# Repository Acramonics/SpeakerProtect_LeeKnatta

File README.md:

Speaker protect circuit from Lee Knatta
https://www.diyaudio.com/community/threads/improved-speaker-protection-circuit.302384/page-6

### PSU:

The power supply is just a full bridge rectifier with storage capacitor. The capacitor C81 should be large and able to withstand the voltage.
The AC loss detection uses half bridge rectifier D81 and D82 to make Q80 conduct and prevent C82 from charging up.
Once the AC fails, C82 charges through R83 and Q81 starts conducting. The "shutdown" is triggered by pulling low.

Assembly notes:
R82 is somewhat superfluous and could be left away with R81 = 100k instead. There are many such useless resistors in the design.
R84 aims to limit discharge current of C82 and may not be really necessary given that Q80 collector current is limited by the large value of R81.
R80 and C80 are optional and just a snubber for taming resonance of the transformer with the rectifier bridge. For now, I didn't install those components.

Debug:
Apply AC to the circuit and measure the supply voltage. Should be 1.4*Vac minus 1V4.
Also install (pull-up) resistor R1 (different schematic page) and measure the voltage at the "shutdown" terminal = supply voltage.
After removal of the AC, the voltage at the at the shutdown terminal should fall to 0V quickly while the supply voltage declines slowly.

### Startup Delay

Resistor R1 charges capacitor C1 until the voltage is high enough for the Schmid trigger Q1 / Q2 to change state.
R2 is just for limiting discharge current in case the "shutdown" terminal is used by external switches / relays to avoid contact damage.
I revised the resistor values around the Schmid trigger to improve low voltage operation.

Notes:
Q4 and Q5 were added to enable DC detection only after the start-up so that DC events during start-up don't trigger the circuitry. This seemed a good idea with the "latch" mode operation enabled, but is a brain fart because once a DC event occurs, the DC detection circuitry is being disabled and may not be able to discharge C1 enough. Furthermore, if the DC error persists (blown output stage) the circuitry enters a hiccup mode, which is highly undesirable. Short Q4 and Q5 as illustrated.
I came to the conclusion that the "latch" mode is not such a great idea for typical applications. More on this on another page.

Debug:
The start-up delay is roughly 12 seconds with the component values shown.
After the delay, the voltage at the collector of Q2 goes high, enabling attached circuitry (if any).
On AC loss, the voltage should go low quickly.

### Status indication and latch

You may recognize that there are two current sources that can be switched on by pulling R23 / R26 low, thus enabling the reference voltage generation of the CCS.
The DC detection connects to the left through R20 and R21.
In case of a DC event, Q20 + Q21 output a few mA into the red LED that indicates that there is a DC error at the moment.
At the same time, Q22 and Q23 output a few mA into the yellow LED and if the components around Q24 are installed, the Q22 / Q23 CCS is kept on after C20 has charged up. The circuitry around Q24 is for the latch operation and keeps the Q22 / Q23 CCS on until switch S1 resets the latch.
The whole LED indicator and latch circuitry has been helpful in the past to debug the operation, but it is kind of impractical to manually reset the circuit in case a DC event has happened. On the other hand side, such events should be very rare. Without the latch enabled, the module re-connects the loudspeaker 12 seconds after the DC error has cleared. No issues with hiccup here. LED indicators are nice, but require a lot of components.

This time, I neither wanted any LED indicators, nor latch operation and just installed R20 + R21 and wired the cathode of D20 to the collector of Q25, bypassing all the circuitry on this page.

There are two options of LED indicators (if desired):
The traffic light thee color LED that makes most sense with the latch mode and a plain red / green LED.
For the R / G LED, the red one takes the place of the yellow one, thus the Q20 / Q21 circuitry should be left away.

3 LED colors:
Green = Loudspeaker connected, everything okay
Red = Acute DC error, loudspeaker disconnected
Yellow = Acute DC error and once red is off: DC error history, loudspeaker disconnected

2 LED colors:
Green = Loudspeaker connected, everything okay
Red = Either acute DC error or DC error history, loudspeaker disconnected

### DC Detection

Here is the DC detection of the left channel. The right channel is identical.

I reverted some connections back to the initial scheme, got rid of some useless components and optimized some component values.
Note that all crossed out components are superfluous and not installed.
I believe I explained the circuit earlier, but here we go again:

Q42 / Q44 and Q43 / Q45 are just current sources, which are switched on by Q40 / Q41 if the amplifier output (left side of the schematic) is DC long enough to charge C40 through R40.
C40 should be >33uF and <56uF. I installed 56uF.
I haven't completed AC tests, thus C41 / C42 are not optimized. A few nF / tens of nF may help to avoid false triggering on high frequency signals. If optimized, this bug may be a feature for oscillation detection maybe. Simulation shows that the detection is less sensitive to high frequencies with updated component values, thus maybe it even works well without C41 / C42.
The two CCS drive current through U40 and U41, which then activate the circuitry on the previous schematic page by pulling low the "DC_FAULT" node.

Galvanic isolation of U40 / U41 is great, but has a price (commercially). There is no need for low on resistance of the opto-couplers, which allows to pick cheaper ones.

DC detection threshold is roughly 3V3. This is good because it avoids false triggering on asymmetric signals (some music may be asymmetric) and this is bad because in case the amplifier has huge DC offset, the drivers may be damaged even at low voltage. There are more sensitive DC detection circuits in case this is a concern.

### Solid state relays

Now both photovoltaic drivers are controlled by the same current source Q60 / Q61.
The current source is switched on by the Schmid trigger.
Having the drivers in series also increases the minimum supply voltage required: The module works with >6VDC.
The output voltage of the photovoltaic drivers should be 13-14V roughly.

Power MOSFETs need to be chosen according to amplifier supply voltage / power and market situation.
Vds needs to be higher than the rail to rail power supply voltage. Lowest on resistance is desirable for lowest distortion.

The 18V Zeners protect the gates and the MOVs should be rated lower than the Vds of the MOSFET.

If the module is powered with >50V roughly, Q61 should have a small radiator.

Note the symbol for U60 / U61 is weird because I designed SMD / THT combo footprint and this is why there are 16 terminals.

# OK light

This would be the optional green LED indicating that everything is okay:

Q70 switches on the CCS Q71 / Q72, which dumps a few mA through the green LED.
Nothing special.

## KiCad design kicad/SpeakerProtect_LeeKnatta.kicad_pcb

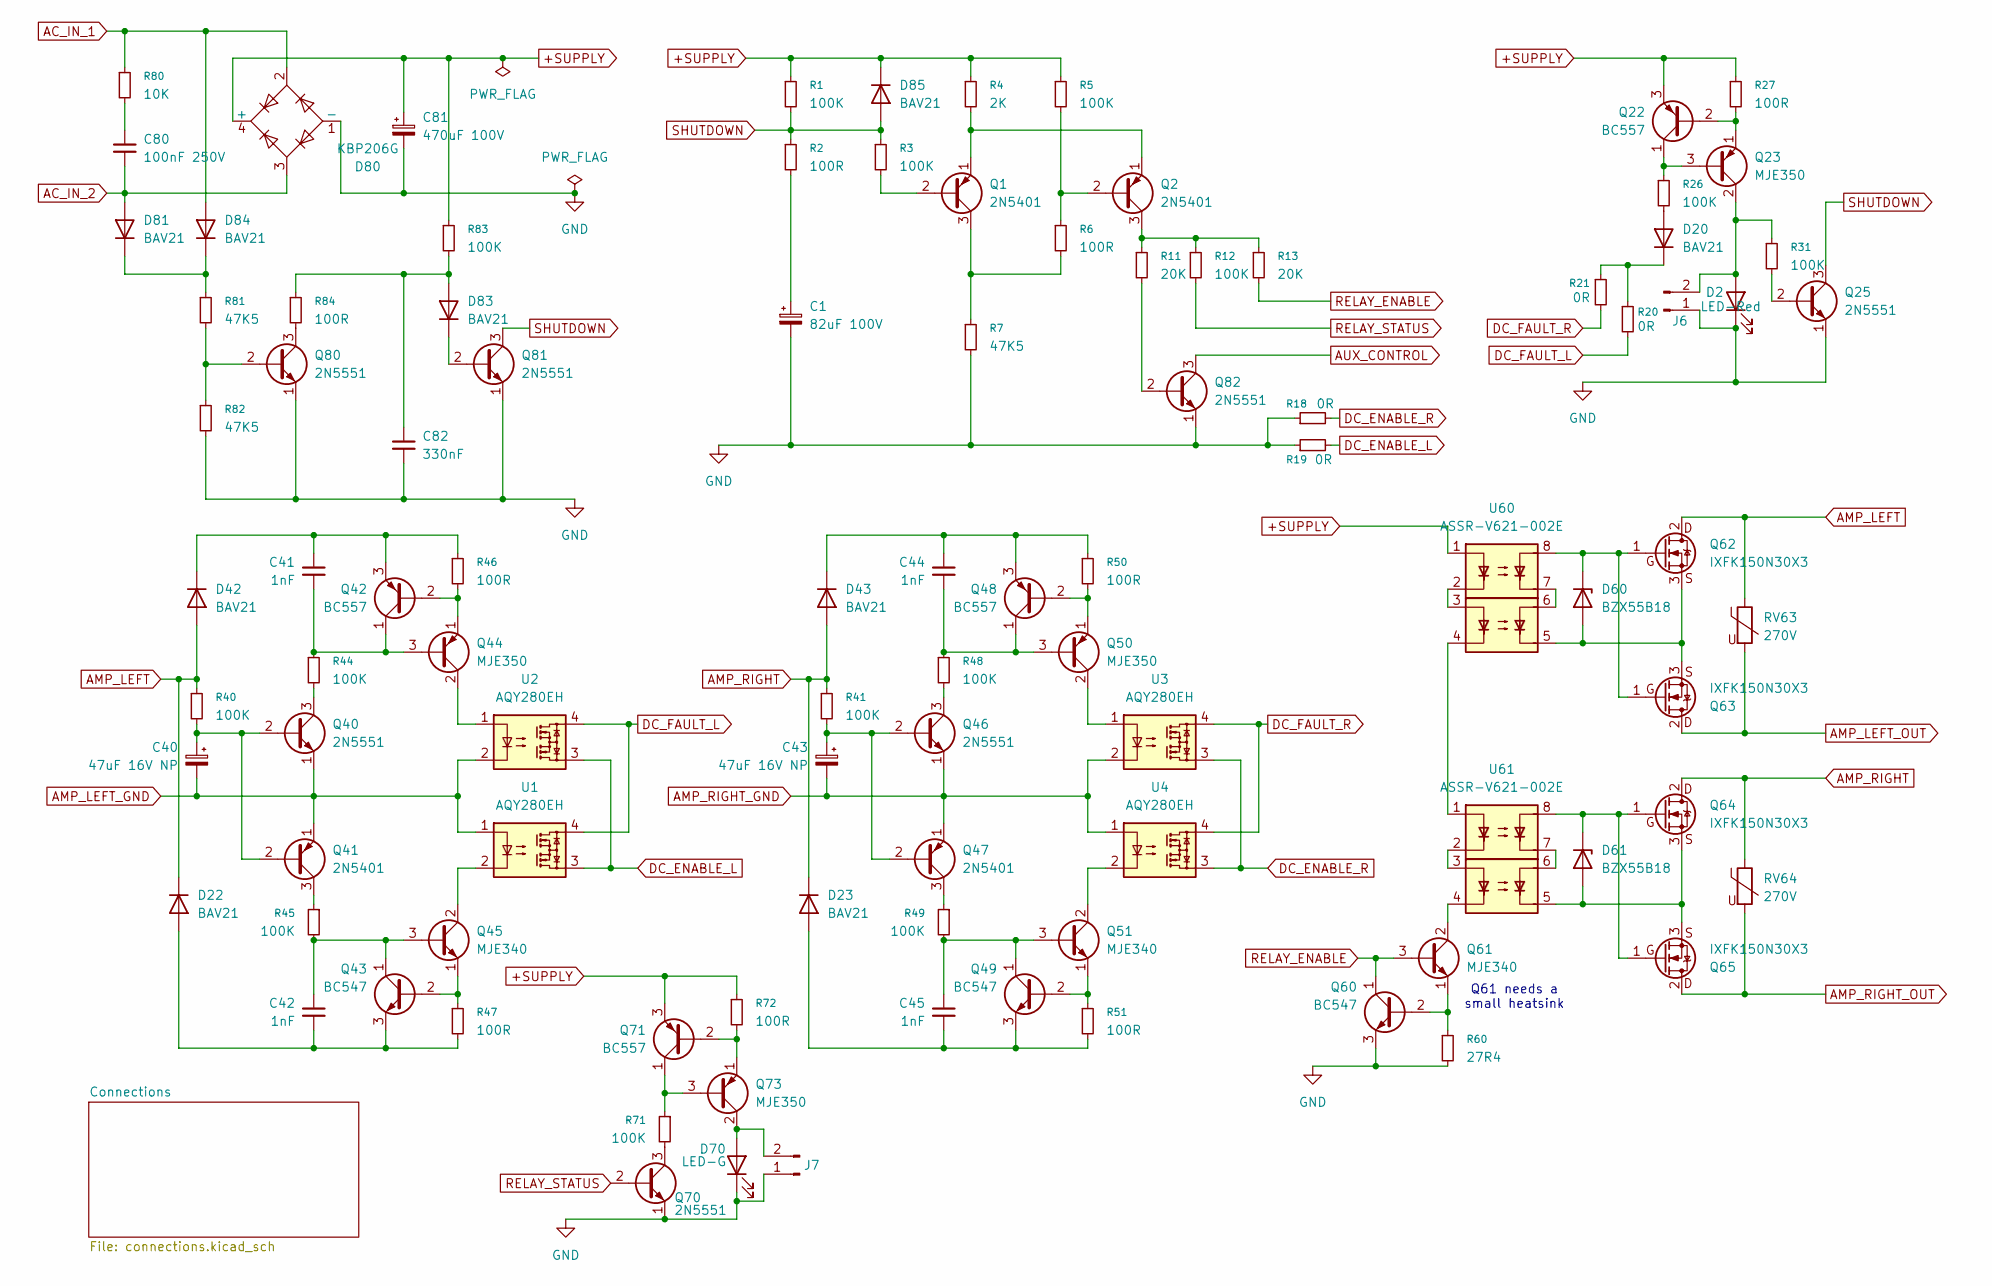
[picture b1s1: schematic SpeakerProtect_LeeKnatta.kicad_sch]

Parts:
C1: 82uF 100V; CP_Radial_D10.0mm_P5.00mm_P7.50mm
C40, C43: 47uF 16V NP; CP_Radial_D5.0mm_P2.00mm
C41, C42, C44, C45: 1nF; C_Rect_L7.0mm_W4.5mm_P5.00mm
C80: 100nF 250V; C_Rect_L7.2mm_W5.0mm_P5.00mm
C81: 470uF 100V; CP_Radial_D16.0mm_P7.50mm
C82: 330nF; C_Rect_L7.0mm_W4.5mm_P5.00mm
D2: LED-Red
D20, D22, D23, D42, D43, D81, D84, D85: BAV21; D_DO-35_SOD27_P7.62mm_Horizontal
D60, D61: BZX55B18; D_DO-35_SOD27_P7.62mm_Horizontal
D70: LED-G
D80: KBP206G; Diode_Bridge_14.5x3.5x10.5mm_P3.61
D83: BAV21; D_DO-41_SOD81_P2.54mm_Vertical_CathodeUp
J6, J7: Conn_01x02_Pin; TerminalBlock_4Ucon_1x02_P3.50mm_Horizontal
Q1, Q2, Q41, Q47: 2N5401; TO-92_Inline_Wide
Q22, Q42, Q48, Q71: BC557; TO-92_Inline_Wide
Q23, Q44, Q50, Q73: MJE350; TO-126-3_Vertical
Q25, Q40, Q46, Q70, Q80, Q81, Q82: 2N5551; TO-92_Inline_Wide
Q43, Q49, Q60: BC547; TO-92_Inline_Wide
Q45, Q51, Q61: MJE340; TO-126-3_Vertical
Q62, Q63, Q64, Q65: IXFK150N30X3; TO-247-3_Vertical
R1, R3, R5, R12, R26, R31, R40, R41, R44, R45, R48, R49, R71, R83: 100K; R_Axial_DIN0207_L6.3mm_D2.5mm_P10.16mm_Horizontal
R2, R6, R27, R84: 100R; R_Axial_DIN0207_L6.3mm_D2.5mm_P10.16mm_Horizontal
R4: 2K; R_Axial_DIN0207_L6.3mm_D2.5mm_P10.16mm_Horizontal
R7, R82: 47K5; R_Axial_DIN0207_L6.3mm_D2.5mm_P10.16mm_Horizontal
R11, R13: 20K; R_Axial_DIN0207_L6.3mm_D2.5mm_P10.16mm_Horizontal
R18, R19, R20, R21: 0R; R_Axial_DIN0207_L6.3mm_D2.5mm_P10.16mm_Horizontal
R46, R47, R50, R51, R72: 100R; R_Axial_DIN0207_L6.3mm_D2.5mm_P2.54mm_Vertical
R60: 27R4; R_Axial_DIN0207_L6.3mm_D2.5mm_P10.16mm_Horizontal
R80: 10K; R_Axial_DIN0207_L6.3mm_D2.5mm_P10.16mm_Horizontal
R81: 47K5; R_Axial_DIN0207_L6.3mm_D2.5mm_P2.54mm_Vertical
RV63, RV64: 270V; RV_Disc_D15.5mm_W7.5mm_P7.5mm
U1, U2, U3, U4: AQY280EH; DIP-4_W7.62mm
U60, U61: ASSR-V621-002E; DIP-8_W7.62mm

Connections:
+SUPPLY: C81.1, D80.4 (+), D85.1 (K), Q22.3 (E), Q71.3 (E), R1.1, R4.1, R5.1, R27.1, R72.1, R83.1, U60.1
AC_IN_1: D80.2, D84.2 (A), R80.1; also elsewhere on the board
AC_IN_2: C80.2, D80.3, D81.2 (A); also elsewhere on the board
AMP_LEFT: D22.1 (K), D42.2 (A), Q62.2 (D), R40.1, RV63.1; also elsewhere on the board
AMP_LEFT_GND: C40.2, Q40.1 (E), Q41.1 (E), U1.1, U2.2; also elsewhere on the board
AMP_LEFT_OUT: Q63.2 (D), RV63.2; also elsewhere on the board
AMP_RIGHT: D23.1 (K), D43.2 (A), Q64.2 (D), R41.1, RV64.1; also elsewhere on the board
AMP_RIGHT_GND: C43.2, Q46.1 (E), Q47.1 (E), U3.2, U4.1; also elsewhere on the board
AMP_RIGHT_OUT: Q65.2 (D), RV64.2; also elsewhere on the board
AUX_CONTROL: Q82.3 (C)
DC_ENABLE_L: R19.2, U1.3, U2.3
DC_ENABLE_R: R18.2, U3.3, U4.3
DC_FAULT_L: R20.2, U1.4, U2.4
DC_FAULT_R: R21.2, U3.4, U4.4
GND: C1.2, C81.2, C82.2, D2.1 (K), D70.1 (K), D80.1 (-), J6.1, J7.1, Q25.1 (E), Q60.3 (E), Q70.1 (E), Q80.1 (E), Q81.1 (E), Q82.1 (E), R7.2, R18.1, R19.1, R60.2, R82.2
unnamed: C1.1, R2.2
unnamed: C80.1, R80.2
unnamed: D20.2 (A), R26.2
unnamed: D20.1 (K), R20.1, R21.1
unnamed: C42.2, D22.2 (A), Q43.3 (E), R47.2
unnamed: C45.2, D23.2 (A), Q49.3 (E), R51.2
unnamed: C41.1, D42.1 (K), Q42.3 (E), R46.1
unnamed: C44.1, D43.1 (K), Q48.3 (E), R50.1
unnamed: D60.2 (A), Q62.3 (S), Q63.3 (S), U60.5
unnamed: D60.1 (K), Q62.1 (G), Q63.1 (G), U60.8
unnamed: D61.2 (A), Q64.3 (S), Q65.3 (S), U61.5
unnamed: D61.1 (K), Q64.1 (G), Q65.1 (G), U61.8
unnamed: D81.1 (K), D84.1 (K), R81.1
unnamed: C82.1, D83.2 (A), R83.2, R84.1
unnamed: D83.1 (K), Q81.2 (B)
unnamed: D2.2 (A), J6.2, Q23.2 (C), R31.1
unnamed: D70.2 (A), J7.2, Q73.2 (C)
unnamed: Q1.2 (B), R3.2
unnamed: Q1.3 (C), R6.2, R7.1
unnamed: Q1.1 (E), Q2.1 (E), R4.2
unnamed: Q2.2 (B), R5.2, R6.1
unnamed: Q2.3 (C), R11.1, R12.1, R13.1
unnamed: Q22.2 (B), Q23.1 (E), R27.2
unnamed: Q22.1 (C), Q23.3 (B), R26.1
unnamed: Q25.2 (B), R31.2
unnamed: C40.1, Q40.2 (B), Q41.2 (B), R40.2
unnamed: Q40.3 (C), R44.2
unnamed: Q41.3 (C), R45.1
unnamed: Q42.2 (B), Q44.1 (E), R46.2
unnamed: C41.2, Q42.1 (C), Q44.3 (B), R44.1
unnamed: Q43.2 (B), Q45.1 (E), R47.1
unnamed: C42.1, Q43.1 (C), Q45.3 (B), R45.2
unnamed: Q44.2 (C), U2.1
unnamed: Q45.2 (C), U1.2
unnamed: C43.1, Q46.2 (B), Q47.2 (B), R41.2
unnamed: Q46.3 (C), R48.2
unnamed: Q47.3 (C), R49.1
unnamed: Q48.2 (B), Q50.1 (E), R50.2
unnamed: C44.2, Q48.1 (C), Q50.3 (B), R48.1
unnamed: Q49.2 (B), Q51.1 (E), R51.1
unnamed: C45.1, Q49.1 (C), Q51.3 (B), R49.2
unnamed: Q50.2 (C), U3.1
unnamed: Q51.2 (C), U4.2
unnamed: Q60.2 (B), Q61.1 (E), R60.1
unnamed: Q61.2 (C), U61.4
unnamed: Q70.3 (C), R71.2
unnamed: Q71.2 (B), Q73.1 (E), R72.2
unnamed: Q71.1 (C), Q73.3 (B), R71.1
unnamed: Q80.2 (B), R81.2, R82.1
unnamed: Q80.3 (C), R84.2
unnamed: Q82.2 (B), R11.2
unnamed: U60.2, U60.3
unnamed: U60.4, U61.1
unnamed: U60.6, U60.7
unnamed: U61.2, U61.3
unnamed: U61.6, U61.7
RELAY_ENABLE: Q60.1 (C), Q61.3 (B), R13.2
RELAY_STATUS: Q70.2 (B), R12.2
SHUTDOWN: D85.2 (A), Q25.3 (C), Q81.3 (C), R1.2, R2.1, R3.1

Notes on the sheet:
Q61 needs a small heatsink

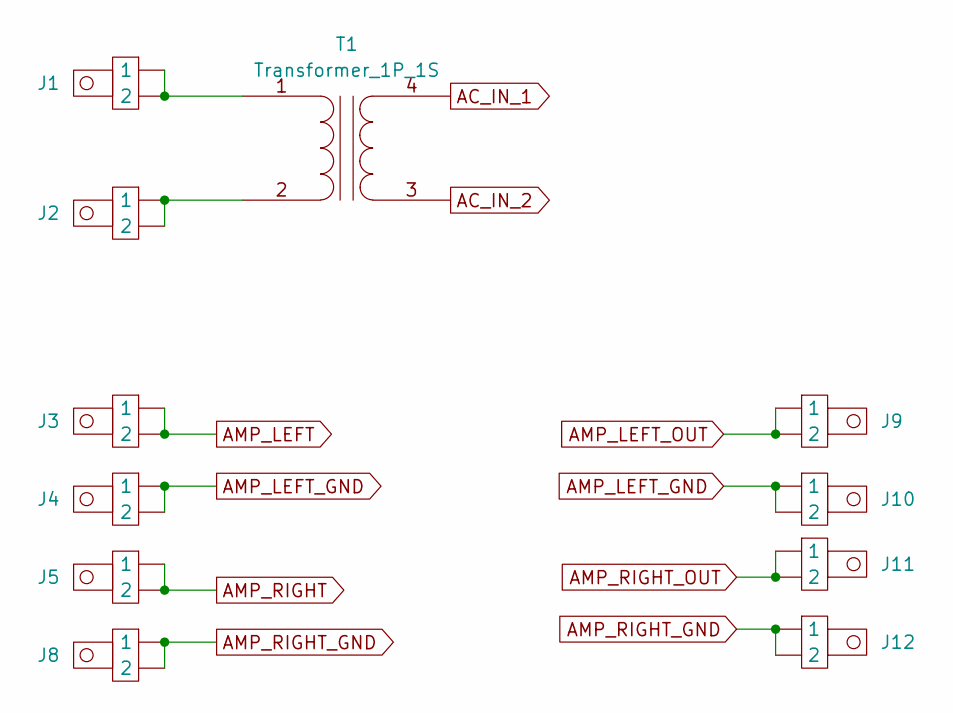
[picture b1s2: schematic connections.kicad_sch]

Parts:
J1, J2, J3, J4, J5, J8, J9, J10, J11, J12: Spade_Connector
T1: Transformer_1P_1S; Transformer_Myrra-44233-230V-18V-5VA-37x44

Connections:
AC_IN_1: T1.4 (SB); also elsewhere on the board
AC_IN_2: T1.3 (SA); also elsewhere on the board
AMP_LEFT: J3.1, J3.2; also elsewhere on the board
AMP_LEFT_GND: J4.1, J4.2, J10.1, J10.2; also elsewhere on the board
AMP_LEFT_OUT: J9.1, J9.2; also elsewhere on the board
AMP_RIGHT: J5.1, J5.2; also elsewhere on the board
AMP_RIGHT_GND: J8.1, J8.2, J12.1, J12.2; also elsewhere on the board
AMP_RIGHT_OUT: J11.1, J11.2; also elsewhere on the board
unnamed: J1.1, J1.2, T1.1 (AA)
unnamed: J2.1, J2.2, T1.2 (AB)

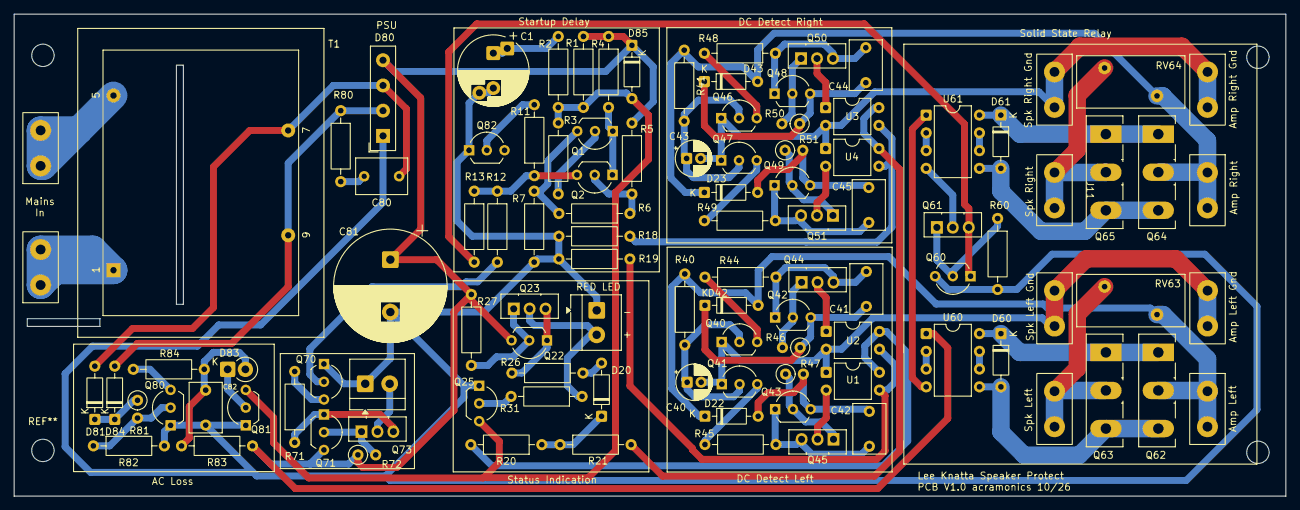
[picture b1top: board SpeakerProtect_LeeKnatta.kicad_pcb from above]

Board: 2 copper layers, 182.0 x 69.0 mm, 107 parts (0 on the bottom side), 75 nets.
